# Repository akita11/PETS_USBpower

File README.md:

# PETS_USBpower

[PETS](https://4ok.jp/pets/)をUSBモバイルバッテリで使えるように改造する部品です。

※PETSを分解・改造して使用します。そのため、PETSの製品保証の対象外となります。

# 用意するもの

※モバイルバッテリ以外の部材はスイッチサイエンスで委託販売予定です

* 筐体の板（2枚）：MDF板（厚さ2.5mm）をレーザーカッター等でカットします。（PETS_USBpower: PDFとInkscape SVGで同一内容）

* USBコネクタ：出っ張りが少ないUSBコネクタ（基板）。USBpowerconn_gerber.zipを基板製造サービス等で製造します（板厚は2.0mmとするか、1.6mmのものに裏面に厚紙などをはさんで厚さを調整する）※ケーブルが根本から切れやすいのでグルーガン等で強化したほうがいいです

* 電源ケーブル：JSTのXHコネクタ(2p)＋10cm程度のケーブル ※[aitendo](http://www.aitendo.com)で売っていることがある

* ダイソーで500円売っているUSBモバイルバッテリ（またはそれと同等のサイズのもの）。サイズは120mm x 70mm x 20mm程度以下であれば、収まります。

# 組み立て

[こちらの手順](https://github.com/akita11/PETS_USBpower/blob/master/instruction/README.md)で、PETSを分解・改造します。改造後は、普段どおりのPETSとして使用できます。

# おまけ

PETSblock_holder.{svg/pdf}をダンボール等でカットして組み立てると、PETSのブロックを保存しておくのに使えます。

# Author

Junichi Akita / @akita11 / akita@ifdl.jp

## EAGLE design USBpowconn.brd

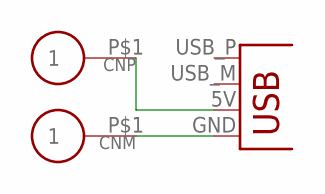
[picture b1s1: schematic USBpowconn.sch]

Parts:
CNM: CON_P01TH09MM; PAD_TH09MM
CNP: CON_P01TH09MM; PAD_TH09MM
JP1: CON_USBPCB; USB-A-PCB

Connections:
unnamed: CNP.P$1, JP1.5V (VBUS)
unnamed: CNM.P$1, JP1.GND

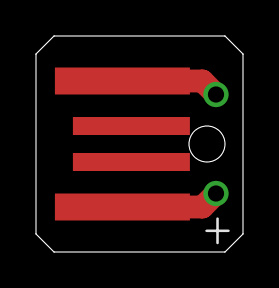
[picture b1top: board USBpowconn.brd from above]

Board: 2 copper layers, 11.5 x 12.0 mm, 3 parts (0 on the bottom side), 2 nets.

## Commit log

2019-07-01 1st commit
2019-07-01 画像URLを修正
2021-03-05 README.mdも誤字を修正
2022-10-05 add instruction
2022-10-05 add block_holder
2022-10-09 add USB connector back
